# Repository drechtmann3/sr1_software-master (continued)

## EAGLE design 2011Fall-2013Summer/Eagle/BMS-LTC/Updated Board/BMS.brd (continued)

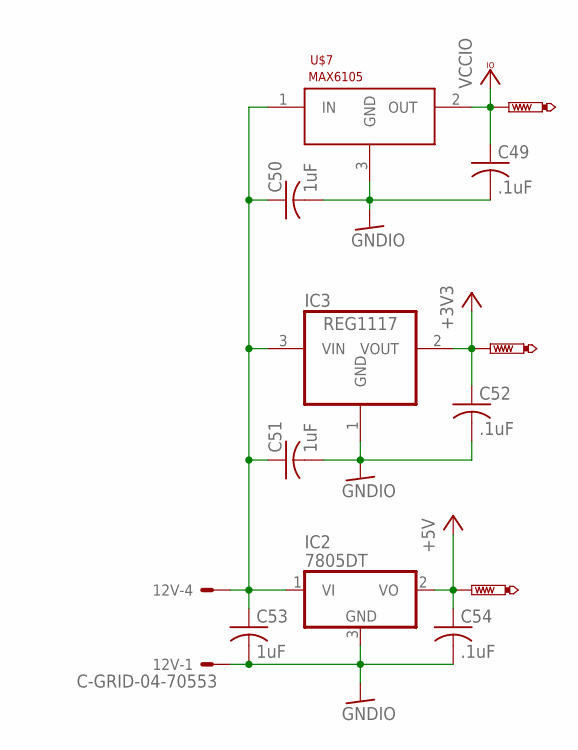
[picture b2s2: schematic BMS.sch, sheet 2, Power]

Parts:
12V: C-GRID-04-70553; 70553-04
C49, C52, C54: .1uF; C1206
C50, C51, C53: 1uF; C1206
IC2: 7805DT; TO252
IC3: REG1117; SOT223
U$7: MAX6105; SOT23
U$11, U$12, U$13: TESTPAD-20MIL; 20MIL

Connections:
12V: 12V.4, C50.1, C51.1, C53.1, IC2.1 (VI), IC3.3 (VIN), U$7.1 (IN); also elsewhere on the board
+3V3: C52.1, IC3.2 (VOUT), U$12.P$1; also elsewhere on the board
+5V: C54.1, IC2.2 (VO), U$13.P$1; also elsewhere on the board
GNDIO: 12V.1, C49.2, C50.2, C51.2, C52.2, C53.2, C54.2, IC2.3 (GND), IC3.1 (GND), U$7.3 (GND); also elsewhere on the board
VCCIO: C49.1, U$7.2 (OUT), U$11.P$1; also elsewhere on the board

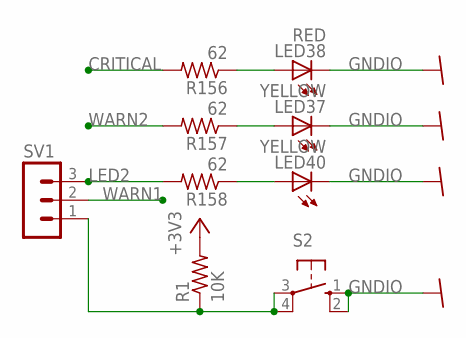
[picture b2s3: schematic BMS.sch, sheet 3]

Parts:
LED37, LED40: YELLOW; CHIPLED_1206
LED38: RED; CHIPLED_1206
R1: 10K; R1206
R156, R157, R158: 62; R1206
S2: 10-XX; B3F-10XX
SV1: MA03-1

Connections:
+3V3: R1.2; also elsewhere on the board
CRITICAL: R156.2; also elsewhere on the board
GNDIO: LED37.C, LED38.C, LED40.C, S2.1 (S), S2.2 (S1); also elsewhere on the board
LED2: R158.2, SV1.3
unnamed: R1.1, S2.3, S2.4 (P1), SV1.1
unnamed: LED37.A, R157.1
unnamed: LED38.A, R156.1
unnamed: LED40.A, R158.1
WARN1: SV1.2; also elsewhere on the board
WARN2: R157.2; also elsewhere on the board

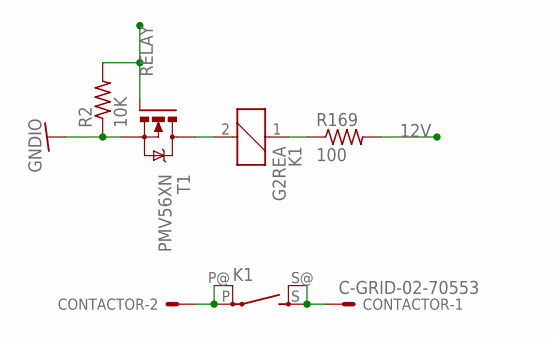
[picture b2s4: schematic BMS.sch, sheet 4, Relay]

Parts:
CONTACTOR: C-GRID-02-70553; 70553-02
K1: G2REA
R2: 10K; R1206
R169: 100; R1206
T1: PMV56XN; SOT23

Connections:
12V: R169.2; also elsewhere on the board
GNDIO: R2.1, T1.2 (S); also elsewhere on the board
unnamed: K1.2, T1.3 (D)
unnamed: K1.1, R169.1
unnamed: CONTACTOR.2, K1.P, K1.P@
unnamed: CONTACTOR.1, K1.S, K1.S@ (S)
RELAY: R2.2, T1.1 (G); also elsewhere on the board

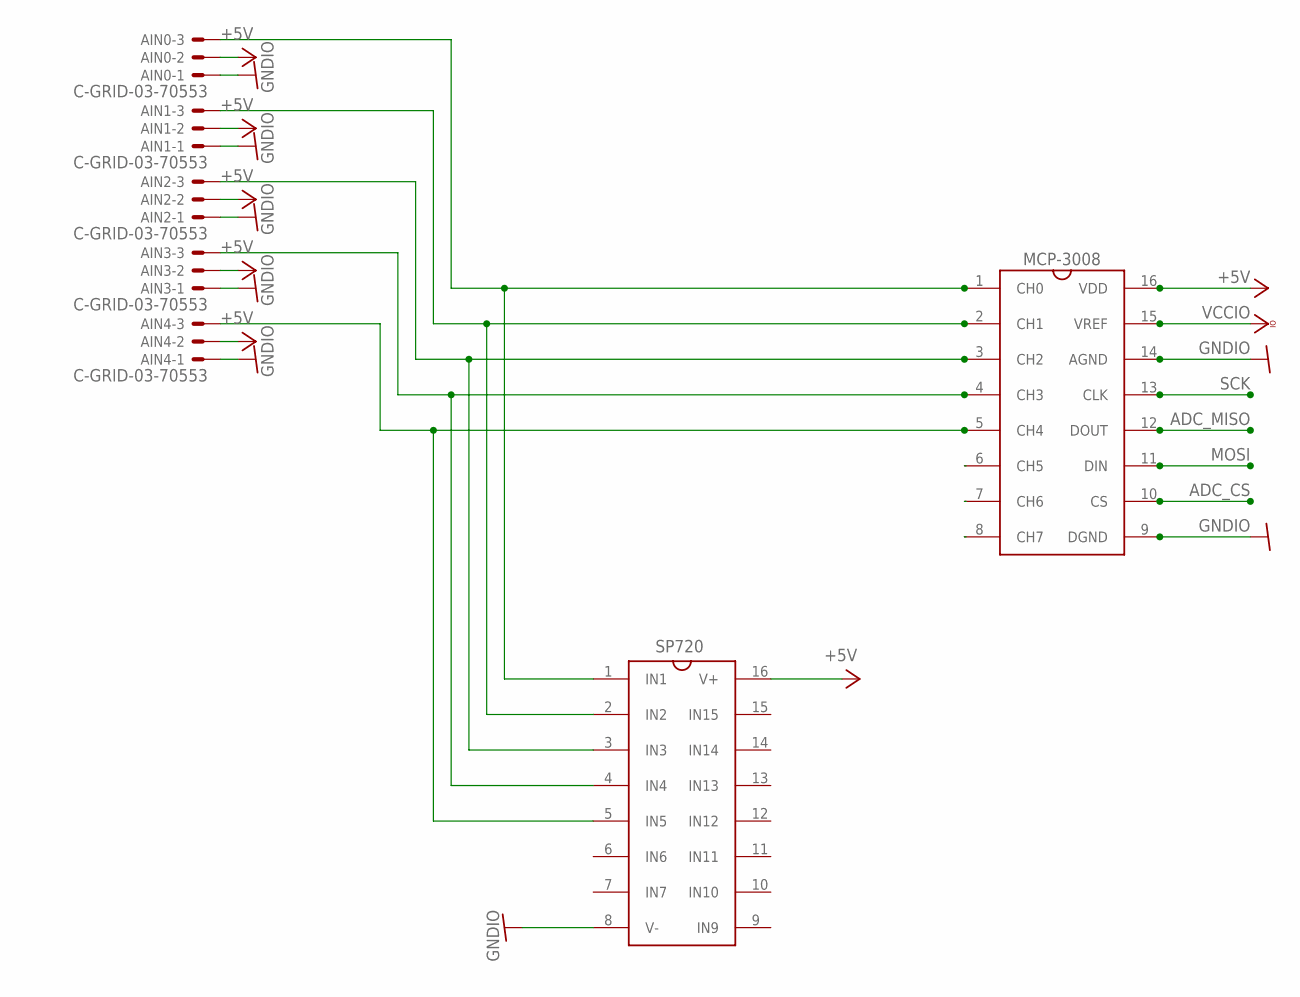
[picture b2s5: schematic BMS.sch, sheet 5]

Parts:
AIN0, AIN1, AIN2, AIN3, AIN4: C-GRID-03-70553; 70553-03
U$1: SP720APP; SO16
U$6: MCP-3008; SO16

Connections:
+5V: AIN0.2, AIN1.2, AIN2.2, AIN3.2, AIN4.2, U$1.16 (V+), U$6.16 (VDD); also elsewhere on the board
ADC_CS: U$6.10 (CS); also elsewhere on the board
ADC_MISO: U$6.12 (DOUT); also elsewhere on the board
GNDIO: AIN0.1, AIN1.1, AIN2.1, AIN3.1, AIN4.1, U$1.8 (V-), U$6.9 (DGND), U$6.14 (AGND); also elsewhere on the board
MOSI: U$6.11 (DIN); also elsewhere on the board
unnamed: AIN0.3, U$1.1 (IN1), U$6.1 (CH0)
unnamed: AIN1.3, U$1.2 (IN2), U$6.2 (CH1)
unnamed: AIN2.3, U$1.3 (IN3), U$6.3 (CH2)
unnamed: AIN3.3, U$1.4 (IN4), U$6.4 (CH3)
unnamed: AIN4.3, U$1.5 (IN5), U$6.5 (CH4)
SCK: U$6.13 (CLK); also elsewhere on the board
VCCIO: U$6.15 (VREF); also elsewhere on the board

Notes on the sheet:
MCP-3008
SP720

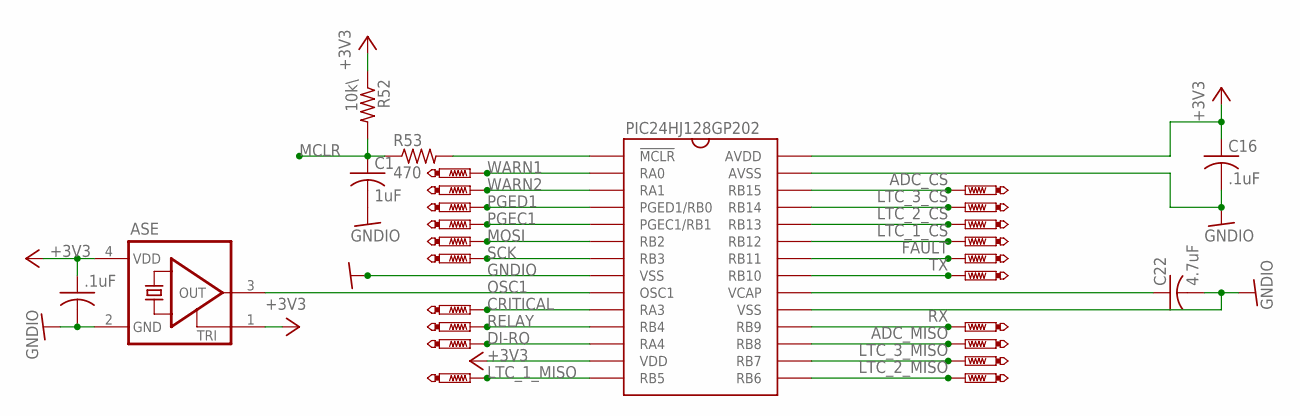
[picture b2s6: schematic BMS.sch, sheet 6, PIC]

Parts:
C1: 1uF; C1206
C16, C48: .1uF; C1206
C22: 4.7uF; C1206
R52: 10k\; R1206
R53: 470; R1206
U$2: PIC24HJ128GP-202; SO28W
U$3: ASE
U$14, U$15, U$16, U$17, U$18, U$19, U$20, U$21, U$22, U$23, U$24, U$25, U$26, U$27, U$28, U$29, U$30, U$31, U$32, U$33: TESTPAD-20MIL; 20MIL

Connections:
+3V3: C16.1, C48.1, R52.1, U$2.13 (VDD), U$2.28 (AVDD), U$3.1 (TRI), U$3.4 (VDD); also elsewhere on the board
ADC_CS: U$2.26 (RB15), U$33.P$1; also elsewhere on the board
ADC_MISO: U$2.17 (RB8), U$26.P$1; also elsewhere on the board
CRITICAL: U$2.10 (RA3), U$20.P$1; also elsewhere on the board
DI-RO: U$2.12 (RA4), U$22.P$1; also elsewhere on the board
FAULT: U$2.22 (RB11), U$29.P$1; also elsewhere on the board
GNDIO: C1.2, C16.2, C22.2, C48.2, U$2.8 (VSS), U$2.19 (VSS), U$2.27 (AVSS), U$3.2 (GND); also elsewhere on the board
LTC_1_CS: U$2.23 (RB12), U$30.P$1; also elsewhere on the board
LTC_1_MISO: U$2.14 (RB5), U$23.P$1; also elsewhere on the board
LTC_2_CS: U$2.24 (RB13), U$31.P$1; also elsewhere on the board
LTC_2_MISO: U$2.15 (RB6), U$24.P$1; also elsewhere on the board
LTC_3_CS: U$2.25 (RB14), U$32.P$1; also elsewhere on the board
LTC_3_MISO: U$2.16 (RB7), U$25.P$1; also elsewhere on the board
MCLR: C1.1, R52.2, R53.1; also elsewhere on the board
MOSI: U$2.6 (RB2), U$18.P$1; also elsewhere on the board
unnamed: R53.2, U$2.1 (!MCLR!)
unnamed: C22.1, U$2.20 (VCAP)
OSC1: U$2.9 (OSC1), U$3.3 (OUT); also elsewhere on the board
PGEC1: U$2.5 (PGEC1/RB1), U$17.P$1; also elsewhere on the board
PGED1: U$2.4 (PGED1/RB0), U$16.P$1; also elsewhere on the board
RELAY: U$2.11 (RB4), U$21.P$1; also elsewhere on the board
RX: U$2.18 (RB9), U$27.P$1; also elsewhere on the board
SCK: U$2.7 (RB3), U$19.P$1; also elsewhere on the board
TX: U$2.21 (RB10), U$28.P$1; also elsewhere on the board
WARN1: U$2.2 (RA0), U$14.P$1; also elsewhere on the board
WARN2: U$2.3 (RA1), U$15.P$1; also elsewhere on the board

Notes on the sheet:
PIC24HJ128GP202

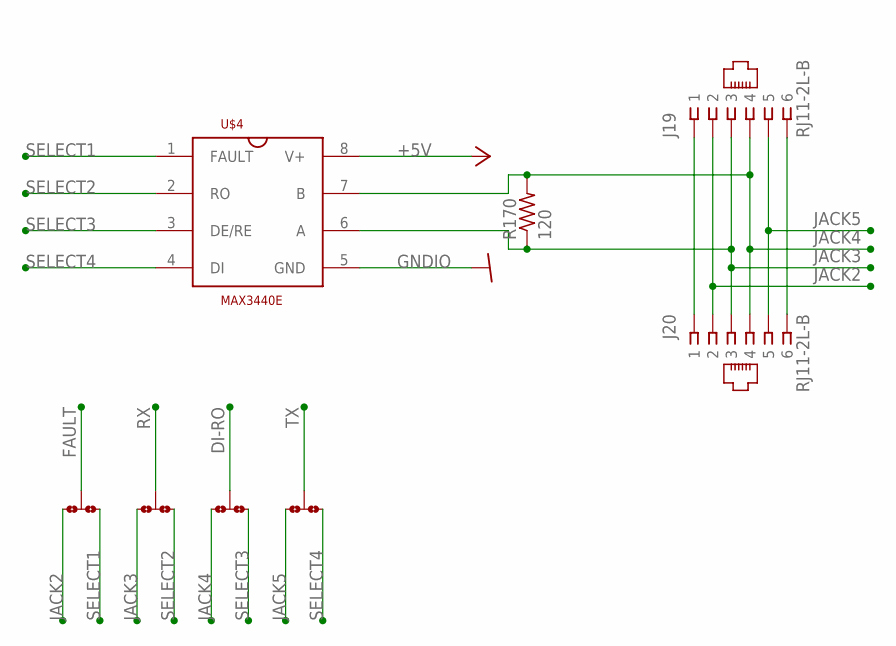
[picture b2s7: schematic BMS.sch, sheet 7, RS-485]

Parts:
J19, J20: RJ11-2L-B; RJ11-NO_SHIELD
R170: 120; R1206
U$4: MAX3440E; SO-08
U$5: 3ROW_4POS

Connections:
+5V: U$4.8 (V+); also elsewhere on the board
DI-RO: U$5.8 (2); also elsewhere on the board
FAULT: U$5.2; also elsewhere on the board
GNDIO: U$4.5 (GND); also elsewhere on the board
JACK2: J19.2, J20.2, U$5.1
JACK3: J19.3, J20.3, R170.1, U$4.6 (A), U$5.4 (1)
JACK4: J19.4, J20.4, R170.2, U$4.7 (B), U$5.7 (1)
JACK5: J19.5, J20.5, U$5.10 (1)
unnamed: J19.1, J20.1
unnamed: J19.6, J20.6
RX: U$5.5 (2); also elsewhere on the board
SELECT1: U$4.1 (FAULT), U$5.3
SELECT2: U$4.2 (RO), U$5.6 (3)
SELECT3: U$4.3 (DE/RE), U$5.9 (3)
SELECT4: U$4.4 (DI), U$5.12 (3)
TX: U$5.11 (2); also elsewhere on the board

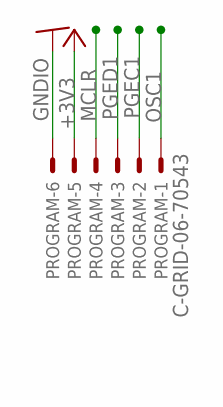
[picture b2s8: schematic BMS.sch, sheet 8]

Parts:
PROGRAM: C-GRID-06-70543; 70543-06

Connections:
+3V3: PROGRAM.5; also elsewhere on the board
GNDIO: PROGRAM.6; also elsewhere on the board
MCLR: PROGRAM.4; also elsewhere on the board
OSC1: PROGRAM.1; also elsewhere on the board
PGEC1: PROGRAM.2; also elsewhere on the board
PGED1: PROGRAM.3; also elsewhere on the board

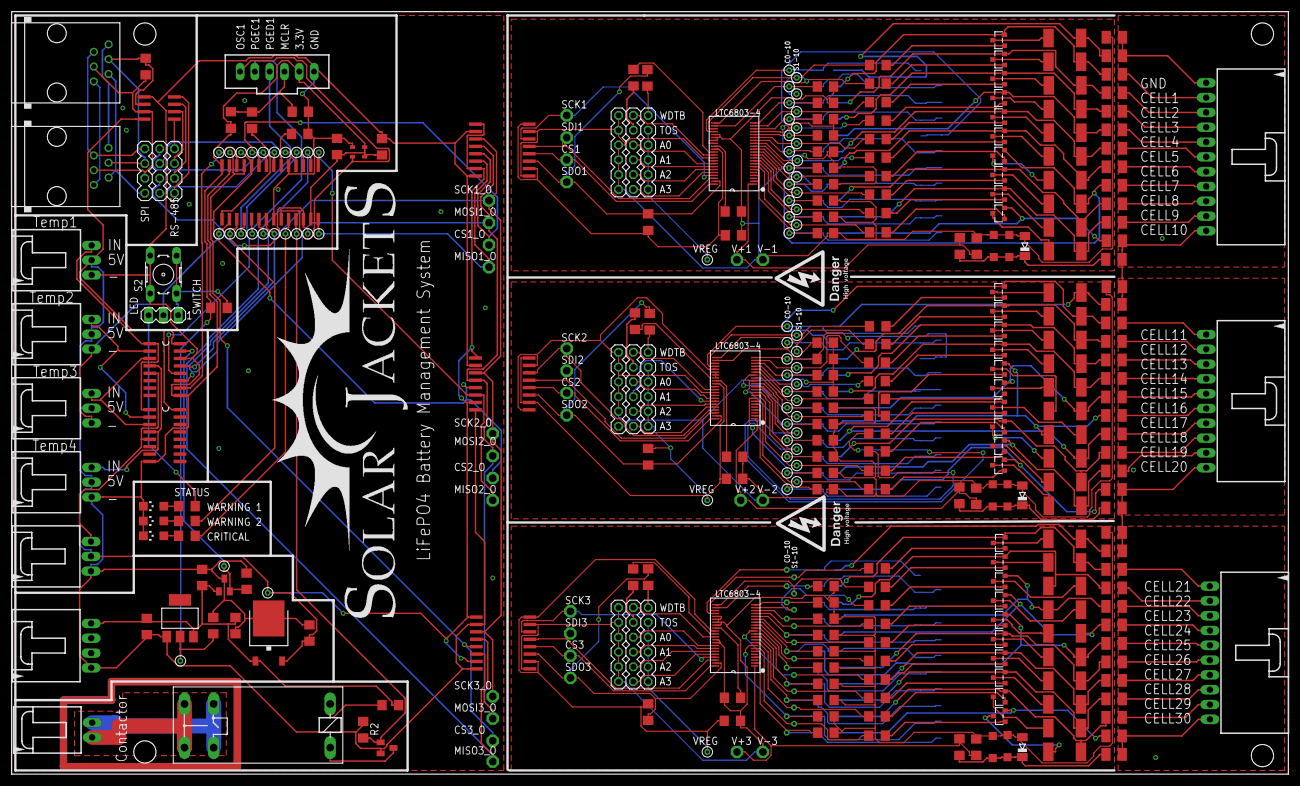
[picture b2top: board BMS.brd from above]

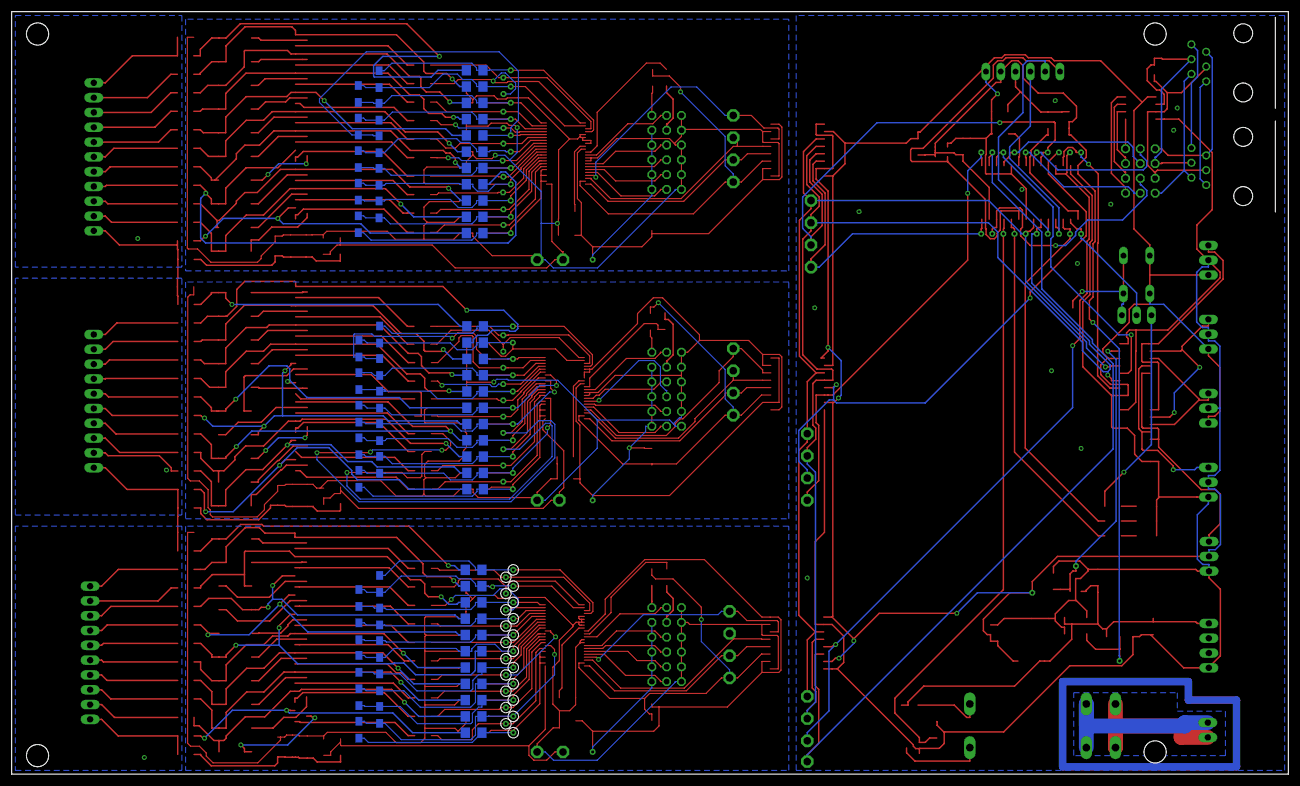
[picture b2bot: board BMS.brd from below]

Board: 2 copper layers, 219.1 x 130.8 mm, 428 parts (84 on the bottom side), 291 nets.

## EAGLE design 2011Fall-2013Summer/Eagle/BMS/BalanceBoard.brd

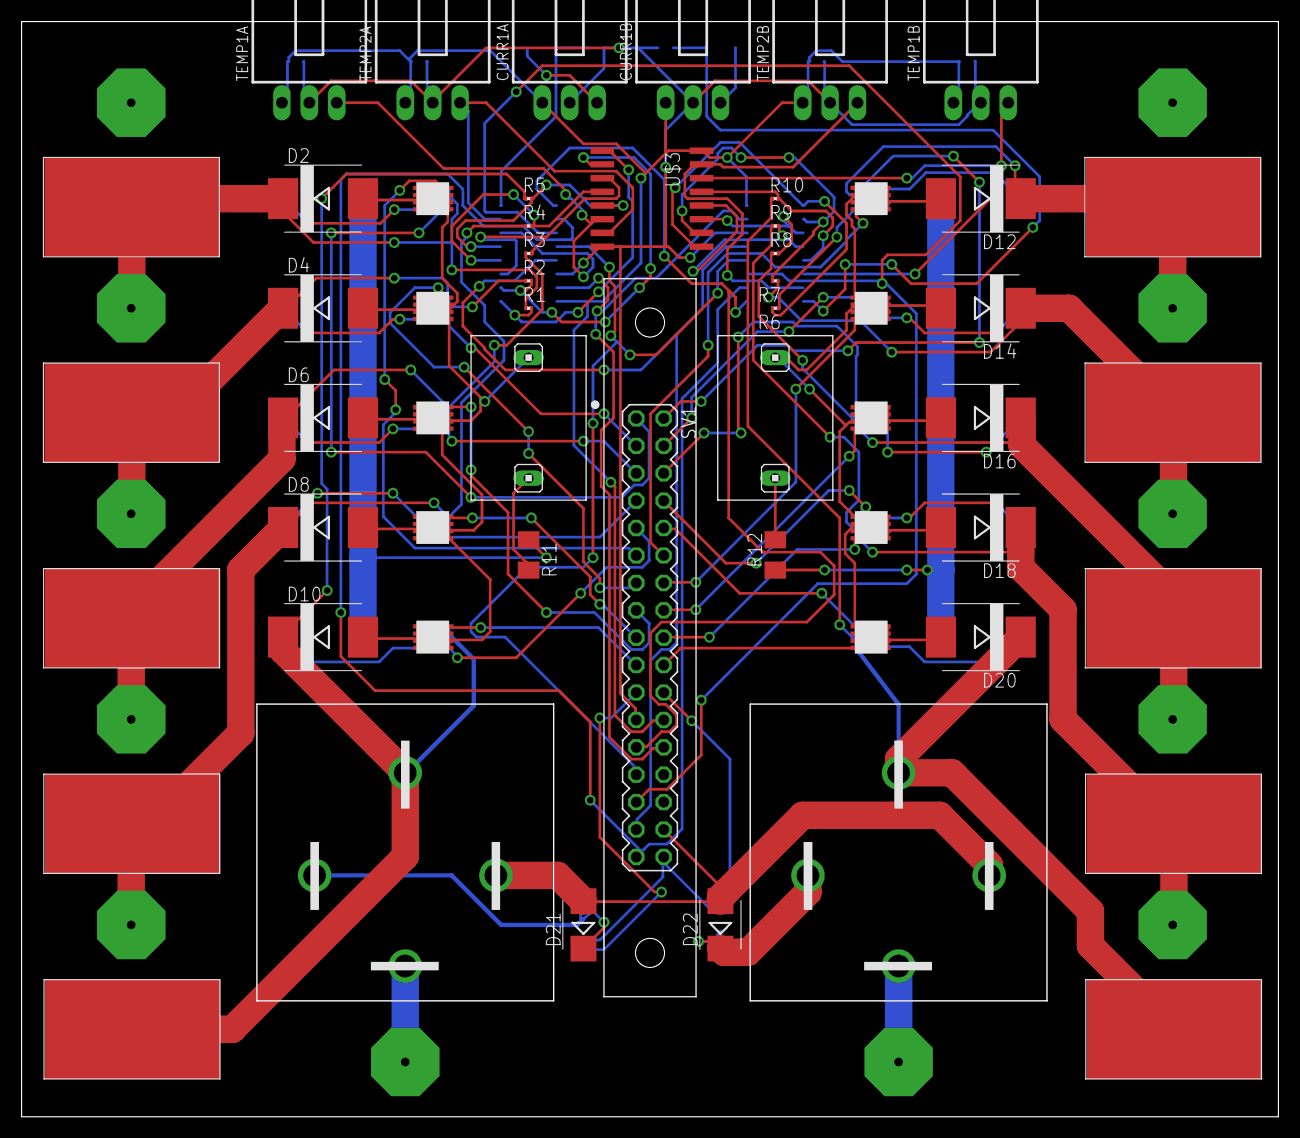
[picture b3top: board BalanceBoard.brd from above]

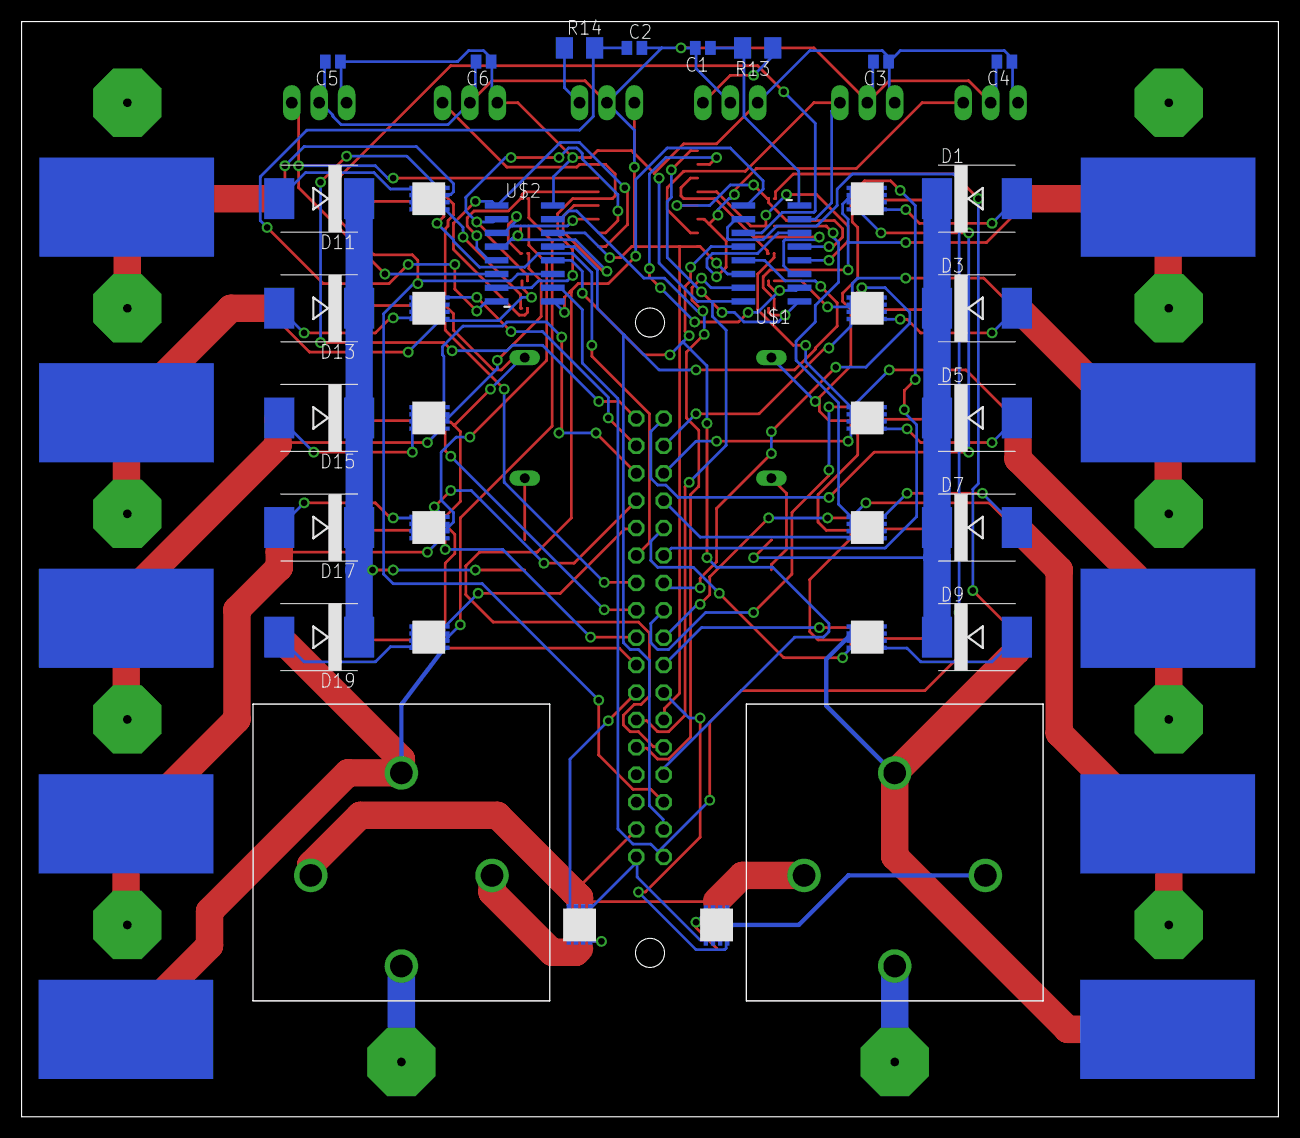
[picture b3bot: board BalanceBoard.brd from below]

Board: 2 copper layers, 116.5 x 101.5 mm, 100 parts (32 on the bottom side), 90 nets.

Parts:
C1, C2, C3, C4, C5, C6: 0.1uF; C0504
CURR1A, CURR1B: C-GRID-03-70553; 70553-03
D1, D2, D3, D4, D5, D6, D7, D8, D9, D10, D11, D12, D13, D14, D15, D16, D17, D18, D19, D20: SMC
D21, D22: SMB
L1, L2: INDUCTOR_SOCKET
R1, R2, R3, R4, R5, R6, R7, R8, R9, R10: 3.3M; R0201
R11, R12: M1206
R13, R14: 1K; M1206
SV1: MA17-2
TEMP1A, TEMP1B, TEMP2A, TEMP2B: C-GRID-03-70553; 70553-03
U$1, U$2: MCP3008; SOIC16N
U$3: SP720APP; SO16W
U$4, U$5, U$6, U$7, U$8, U$9, U$10, U$11, U$12, U$13, U$23, U$26, U$27, U$30, U$31, U$32, U$33, U$34, U$35, U$36, U$37, U$38: SIS322DNT-T1-GE3POWERPAK1212-8; POWERPAK1212-8
U$14, U$15, U$16, U$17, U$18, U$40, U$41, U$42, U$43, U$44: MOLEXCONN-SCREWHOLE
U$20, U$22, U$24, U$25, U$28, U$29, U$46, U$47, U$48, U$49, U$50, U$51: MOLEXCONN-SCREWHOLE-NEG
U$21, U$39: PB1039

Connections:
12V+: SV1.34, U$23.SOURCE1, U$23.SOURCE2, U$23.SOURCE3, U$38.SOURCE1, U$38.SOURCE2, U$38.SOURCE3
12V-: D21.A, D22.A, SV1.32, U$21.P$2, U$39.P$2
AGND_PLANE: C1.2, C2.2, C3.2, C4.2, C5.2, C6.2, CURR1A.2, CURR1B.2, SV1.23, TEMP1A.2, TEMP1B.2, TEMP2A.2, TEMP2B.2, U$1.14, U$2.14, U$3.8
CH0A: D2.C, R1.1, U$4.SOURCE1, U$4.SOURCE2, U$4.SOURCE3, U$14.P$1, U$22.P$1
CH0B: D12.C, R6.1, U$26.SOURCE1, U$26.SOURCE2, U$26.SOURCE3, U$40.P$1, U$47.P$1
CH1A: D4.C, R2.1, U$6.SOURCE1, U$6.SOURCE2, U$6.SOURCE3, U$15.P$1, U$24.P$1
CH1B: D14.C, R7.1, U$30.SOURCE1, U$30.SOURCE2, U$30.SOURCE3, U$41.P$1, U$48.P$1
CH2A: D6.C, R3.1, U$8.SOURCE1, U$8.SOURCE2, U$8.SOURCE3, U$16.P$1, U$25.P$1
CH2B: D16.C, R8.1, U$32.SOURCE1, U$32.SOURCE2, U$32.SOURCE3, U$42.P$1, U$49.P$1
CH3A: D8.C, R4.1, U$10.SOURCE1, U$10.SOURCE2, U$10.SOURCE3, U$17.P$1, U$28.P$1
CH3B: D18.C, R9.1, U$34.SOURCE1, U$34.SOURCE2, U$34.SOURCE3, U$43.P$1, U$50.P$1
CH4A: D10.C, R5.1, U$12.SOURCE1, U$12.SOURCE2, U$12.SOURCE3, U$18.P$1, U$21.P$4
CH4B: D20.C, R10.1, U$36.SOURCE1, U$36.SOURCE2, U$36.SOURCE3, U$39.P$4, U$44.P$1
CH5A: TEMP1A.3, U$1.6, U$3.6
CH5B: TEMP1B.3, U$2.6, U$3.14
CH6A: TEMP2A.3, U$1.7, U$3.7
CH6B: TEMP2B.3, U$2.7, U$3.15
CH7A: C1.1, R13.2, U$1.8
CH7B: C2.1, R14.2, U$2.8
CLK: SV1.31, U$1.13, U$2.13
CS: SV1.33, U$1.10, U$2.10
DGND: SV1.25, U$1.9, U$2.9
DIN: SV1.29, U$1.11, U$2.11
DOUT: SV1.27, U$1.12, U$2.12
unnamed: R5.2, U$1.5, U$3.5
unnamed: R4.2, U$1.4, U$3.4
unnamed: R3.2, U$1.3, U$3.3
unnamed: R2.2, U$1.2, U$3.2
unnamed: R1.2, U$1.1, U$3.1
unnamed: CURR1A.3, R13.1
unnamed: CURR1B.3, R14.1
unnamed: D1.A, U$4.DRAIN5, U$4.DRAIN6, U$4.DRAIN7, U$4.DRAIN8, U$4.DRAIN_ALL
unnamed: R10.2, U$2.5, U$3.13
unnamed: R9.2, U$2.4, U$3.12
unnamed: R8.2, U$2.3, U$3.11
unnamed: R7.2, U$2.2, U$3.10
unnamed: R6.2, U$2.1, U$3.9
unnamed: D2.A, U$5.DRAIN5, U$5.DRAIN6, U$5.DRAIN7, U$5.DRAIN8, U$5.DRAIN_ALL
unnamed: D21.C, U$21.P$3, U$23.DRAIN5, U$23.DRAIN6, U$23.DRAIN7, U$23.DRAIN8, U$23.DRAIN_ALL
unnamed: L1.P$1, R11.2
unnamed: D3.A, U$6.DRAIN5, U$6.DRAIN6, U$6.DRAIN7, U$6.DRAIN8, U$6.DRAIN_ALL
unnamed: D4.A, U$7.DRAIN5, U$7.DRAIN6, U$7.DRAIN7, U$7.DRAIN8, U$7.DRAIN_ALL
unnamed: U$21.P$1, U$29.P$1
unnamed: D11.A, U$26.DRAIN5, U$26.DRAIN6, U$26.DRAIN7, U$26.DRAIN8, U$26.DRAIN_ALL
unnamed: D5.A, U$8.DRAIN5, U$8.DRAIN6, U$8.DRAIN7, U$8.DRAIN8, U$8.DRAIN_ALL
unnamed: D6.A, U$9.DRAIN5, U$9.DRAIN6, U$9.DRAIN7, U$9.DRAIN8, U$9.DRAIN_ALL
unnamed: D12.A, U$27.DRAIN5, U$27.DRAIN6, U$27.DRAIN7, U$27.DRAIN8, U$27.DRAIN_ALL
unnamed: D7.A, U$10.DRAIN5, U$10.DRAIN6, U$10.DRAIN7, U$10.DRAIN8, U$10.DRAIN_ALL
unnamed: D8.A, U$11.DRAIN5, U$11.DRAIN6, U$11.DRAIN7, U$11.DRAIN8, U$11.DRAIN_ALL
unnamed: D13.A, U$30.DRAIN5, U$30.DRAIN6, U$30.DRAIN7, U$30.DRAIN8, U$30.DRAIN_ALL
unnamed: D9.A, U$12.DRAIN5, U$12.DRAIN6, U$12.DRAIN7, U$12.DRAIN8, U$12.DRAIN_ALL
unnamed: D10.A, U$13.DRAIN5, U$13.DRAIN6, U$13.DRAIN7, U$13.DRAIN8, U$13.DRAIN_ALL
unnamed: D14.A, U$31.DRAIN5, U$31.DRAIN6, U$31.DRAIN7, U$31.DRAIN8, U$31.DRAIN_ALL
unnamed: D15.A, U$32.DRAIN5, U$32.DRAIN6, U$32.DRAIN7, U$32.DRAIN8, U$32.DRAIN_ALL
unnamed: D16.A, U$33.DRAIN5, U$33.DRAIN6, U$33.DRAIN7, U$33.DRAIN8, U$33.DRAIN_ALL
unnamed: D17.A, U$34.DRAIN5, U$34.DRAIN6, U$34.DRAIN7, U$34.DRAIN8, U$34.DRAIN_ALL
unnamed: D18.A, U$35.DRAIN5, U$35.DRAIN6, U$35.DRAIN7, U$35.DRAIN8, U$35.DRAIN_ALL
unnamed: D19.A, U$36.DRAIN5, U$36.DRAIN6, U$36.DRAIN7, U$36.DRAIN8, U$36.DRAIN_ALL
unnamed: D20.A, U$37.DRAIN5, U$37.DRAIN6, U$37.DRAIN7, U$37.DRAIN8, U$37.DRAIN_ALL
unnamed: L2.P$2, U$27.SOURCE1, U$27.SOURCE2, U$27.SOURCE3, U$31.SOURCE1, U$31.SOURCE2, U$31.SOURCE3, U$33.SOURCE1, U$33.SOURCE2, U$33.SOURCE3, U$35.SOURCE1, U$35.SOURCE2, U$35.SOURCE3, U$37.SOURCE1, U$37.SOURCE2, U$37.SOURCE3
unnamed: U$39.P$1, U$51.P$1
unnamed: D22.C, U$38.DRAIN5, U$38.DRAIN6, U$38.DRAIN7, U$38.DRAIN8, U$38.DRAIN_ALL, U$39.P$3
unnamed: D11.C, D13.C, D15.C, D17.C, D19.C, R12.1
unnamed: L2.P$1, R12.2
unnamed: L1.P$2, U$5.SOURCE1, U$5.SOURCE2, U$5.SOURCE3, U$7.SOURCE1, U$7.SOURCE2, U$7.SOURCE3, U$9.SOURCE1, U$9.SOURCE2, U$9.SOURCE3, U$11.SOURCE1, U$11.SOURCE2, U$11.SOURCE3, U$13.SOURCE1, U$13.SOURCE2, U$13.SOURCE3
unnamed: D1.C, D3.C, D5.C, D7.C, D9.C, R11.1
RELAYA: SV1.21, U$23.GATE
RELAYB: SV1.22, U$38.GATE
VDD_PLANE: C3.1, C4.1, C5.1, C6.1, CURR1A.1, CURR1B.1, SV1.24, TEMP1A.1, TEMP1B.1, TEMP2A.1, TEMP2B.1, U$1.16, U$2.16, U$3.16
VREF: SV1.26, U$1.15, U$2.15
X0A: SV1.1, U$4.GATE
X0B: SV1.2, U$26.GATE
X1A: SV1.3, U$6.GATE
X1B: SV1.4, U$30.GATE
X2A: SV1.5, U$8.GATE
X2B: SV1.6, U$32.GATE
X3A: SV1.7, U$10.GATE
X3B: SV1.8, U$34.GATE
X4A: SV1.9, U$12.GATE
X4B: SV1.10, U$36.GATE
Y0A: SV1.11, U$5.GATE
Y0B: SV1.12, U$27.GATE
Y1A: SV1.13, U$7.GATE
Y1B: SV1.14, U$31.GATE
Y2A: SV1.15, U$9.GATE
Y2B: SV1.16, U$33.GATE
Y3A: SV1.17, U$11.GATE
Y3B: SV1.18, U$35.GATE
Y4A: SV1.19, U$13.GATE
Y4B: SV1.20, U$37.GATE

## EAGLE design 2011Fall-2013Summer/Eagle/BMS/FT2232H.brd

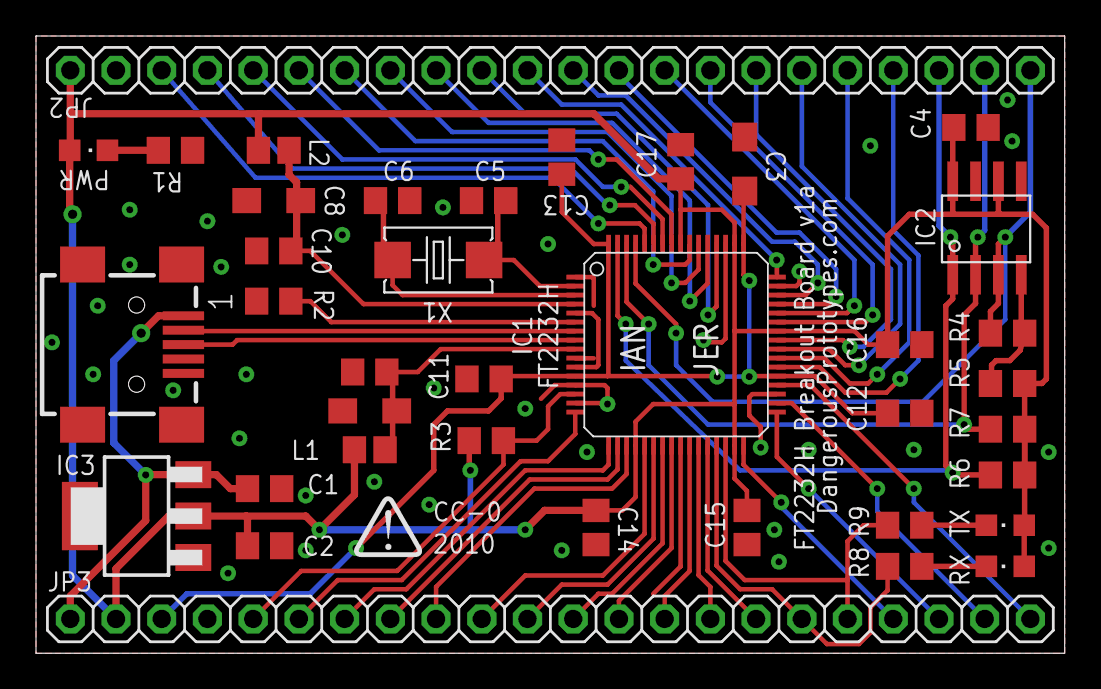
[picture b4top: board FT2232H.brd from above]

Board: 2 copper layers, 57.1 x 34.3 mm, 39 parts (0 on the bottom side), 53 nets.

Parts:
C1, C2, C4, C9, C10, C11, C12, C13, C14, C15, C16, C17: 0.1uF; C805
C3: 3.3uF; SMC_A
C5, C6: 27pF; C805
C7, C8: 4.7uF; SMC_A
CONN1: CONN_USB; CONN_USB_MINI-B
IC1: FT2232H; LQFP64
IC2: 93C46; SOIC8
IC3: SOT223
JP2, JP3: 1X22
L1, L2: FB805
PWR: LED-805
R1, R8, R9: 470; R805
R2: 12k 1%; R805
R3, R5, R6, R7: 10k; R805
R4: 2.2k; R805
RX: LED-805
TX: LED-805
U$7: DP_LOGO
X1: 12MHz; 4X6

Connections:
1.8V: C3.+, C11.1, C12.1, C13.1, IC1.12, IC1.37, IC1.49, IC1.64, JP3.3
3.3V: C2.1, C4.1, C14.1, C15.1, C16.1, C17.1, IC1.20, IC1.31, IC1.42, IC1.50, IC1.56, IC2.6, IC2.8, IC3.2, JP2.1, JP3.2, L1.2, L2.2, PWR.A, R3.1, R5.2, R6.2, R7.2, RX.A, TX.A
5V: C1.1, CONN1.VUSB, IC3.3, JP3.1
!PWEREN: IC1.60, JP2.3
!RESET: IC1.14, JP3.5, R3.2
!SUSPEND: IC1.36, JP3.22
AC0: IC1.26, JP3.14
AC1: IC1.27, JP3.15
AC2: IC1.28, JP3.16
AC3: IC1.29, JP3.17, R8.1
AC4: IC1.30, JP3.18, R9.1
AC5: IC1.32, JP3.19
AC6: IC1.33, JP3.20
AC7: IC1.34, JP3.21
AD0: IC1.16, JP3.6
AD1: IC1.17, JP3.7
AD2: IC1.18, JP3.8
AD3: IC1.19, JP3.9
AD4: IC1.21, JP3.10
AD5: IC1.22, JP3.11
AD6: IC1.23, JP3.12
AD7: IC1.24, JP3.13
BC0: IC1.48, JP2.11
BC1: IC1.52, JP2.10
BC2: IC1.53, JP2.9
BC3: IC1.54, JP2.8
BC4: IC1.55, JP2.7
BC5: IC1.57, JP2.6
BC6: IC1.58, JP2.5
BC7: IC1.59, JP2.4
BD0: IC1.38, JP2.19
BD1: IC1.39, JP2.18
BD2: IC1.40, JP2.17
BD3: IC1.41, JP2.16
BD4: IC1.43, JP2.15
BD5: IC1.44, JP2.14
BD6: IC1.45, JP2.13
BD7: IC1.46, JP2.12
DM: CONN1.D-, IC1.7
DP: CONN1.D+, IC1.8
EECLK: IC1.62, IC2.2, JP2.21, R7.1
EECS: IC1.63, IC2.1, JP2.20, R6.1
EEDATA: IC1.61, IC2.3, JP2.22, R4.2
GND: C1.2, C2.2, C3.-, C4.2, C5.2, C6.2, C7.-, C8.-, C9.2, C10.2, C11.2, C12.2, C13.2, C14.2, C15.2, C16.2, C17.2, CONN1.GND, IC1.1, IC1.5, IC1.10, IC1.11, IC1.13, IC1.15, IC1.25, IC1.35, IC1.47, IC1.51, IC2.5, IC3.1, JP2.2, JP3.4, R1.1, R2.1
unnamed: PWR.C, R1.2
unnamed: R8.2, RX.C
unnamed: R9.2, TX.C
unnamed: IC1.6, R2.2
unnamed: C5.1, IC1.2, X1.1
unnamed: C6.1, IC1.3, X1.2
unnamed: IC2.4, R4.1, R5.1
unnamed: C8.+, C10.1, IC1.4, L2.1
unnamed: C7.+, C9.1, IC1.9, L1.1

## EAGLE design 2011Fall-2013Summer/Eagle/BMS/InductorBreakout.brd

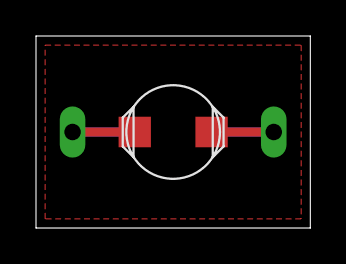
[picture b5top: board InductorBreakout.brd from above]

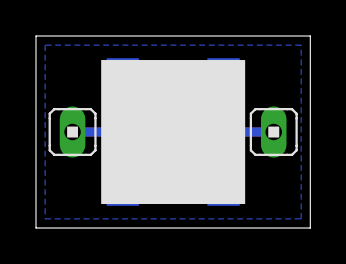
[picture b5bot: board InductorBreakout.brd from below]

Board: 2 copper layers, 15.2 x 10.7 mm, 4 parts (3 on the bottom side), 2 nets.

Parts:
NEWBATT: LQH55PN220MR0L
OLDBATT: NRS8040T0R9NJGJ
U$5, U$6: SINGLE_HEADER

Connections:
unnamed: NEWBATT.P$2, OLDBATT.P$2, U$5.P$1
unnamed: NEWBATT.P$1, OLDBATT.P$1, U$6.P$1

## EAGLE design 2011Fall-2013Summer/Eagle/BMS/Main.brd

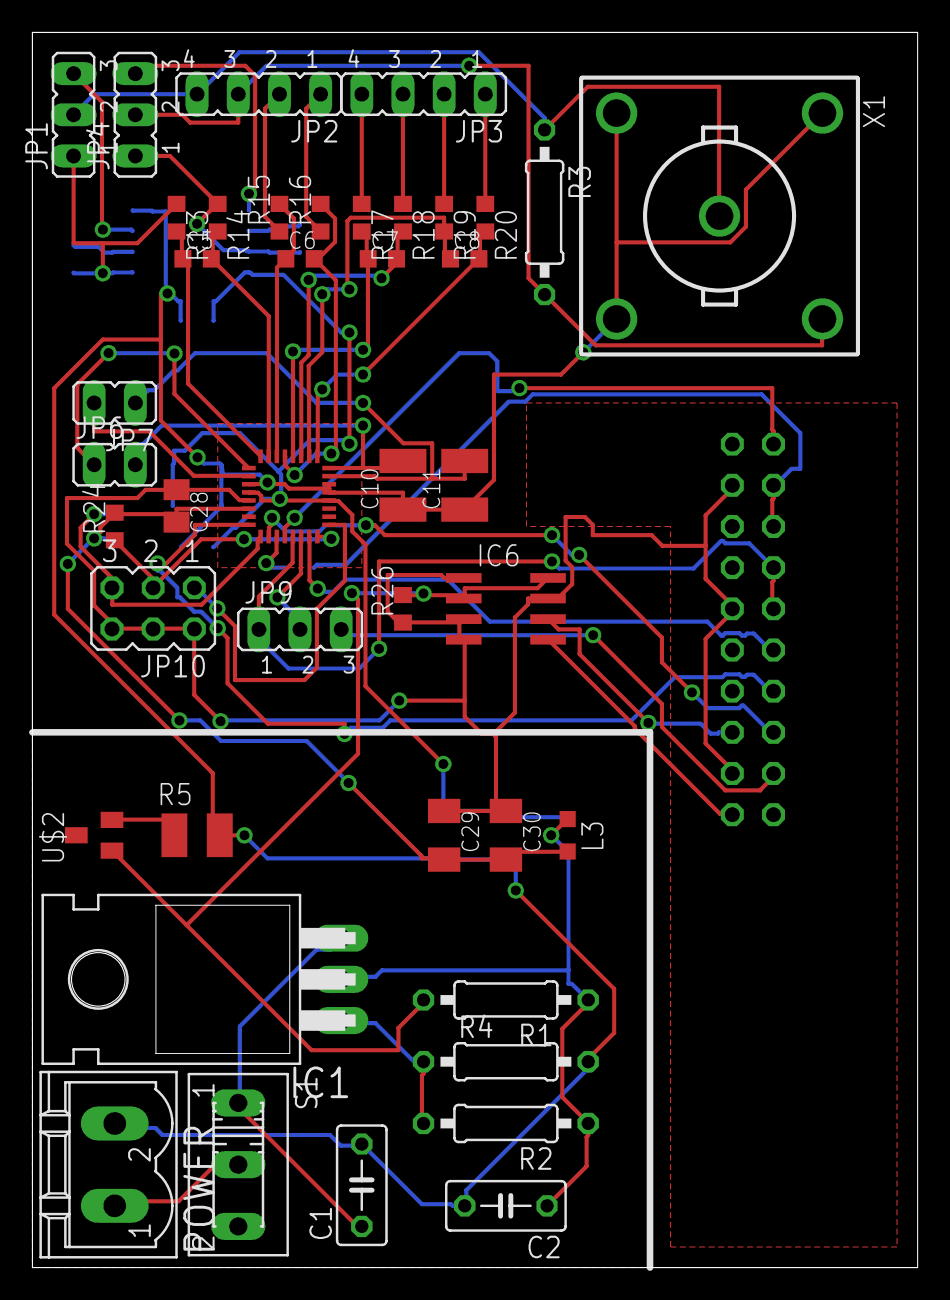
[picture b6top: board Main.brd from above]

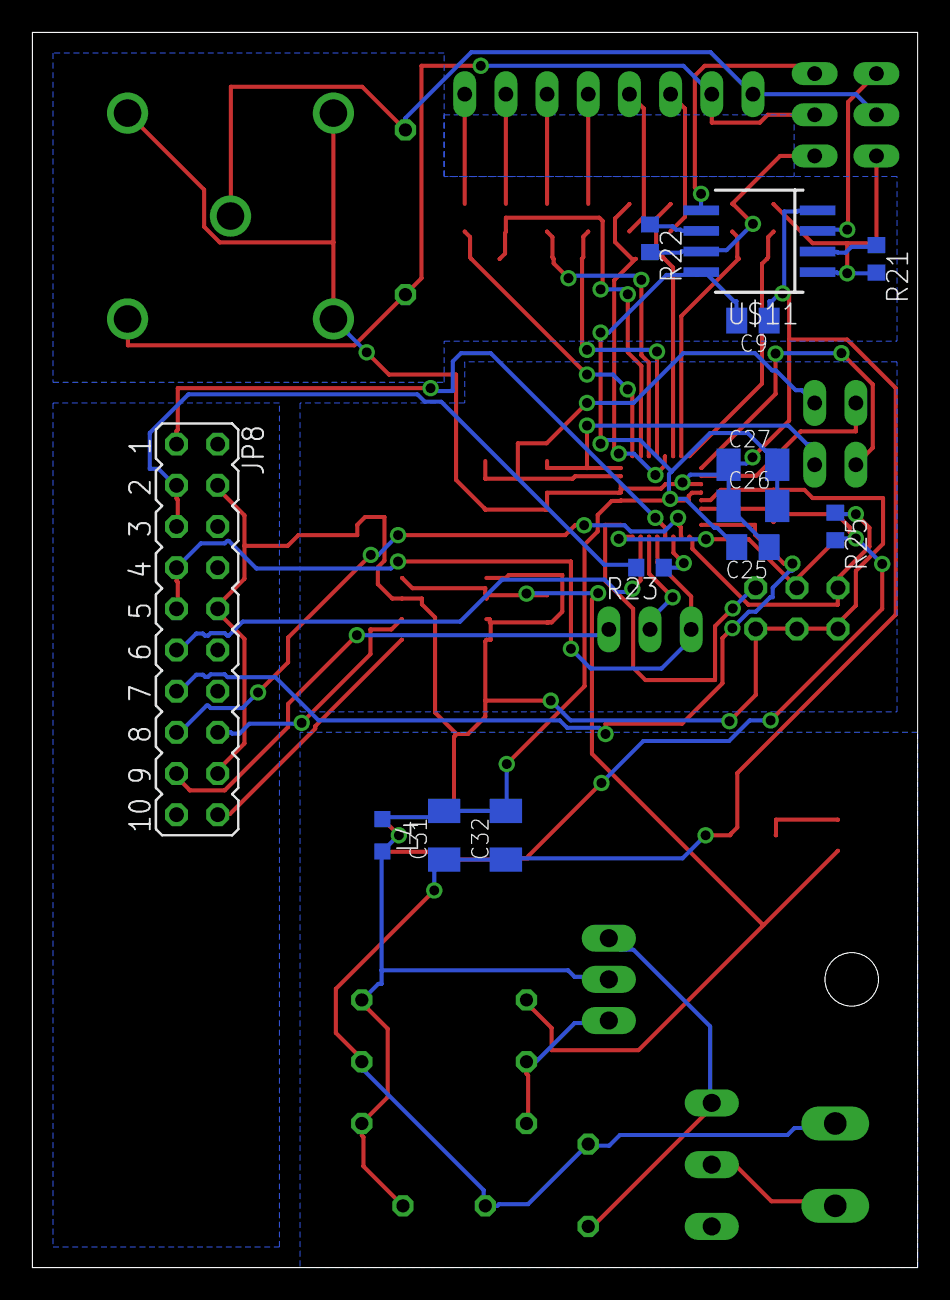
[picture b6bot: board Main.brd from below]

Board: 2 copper layers, 54.6 x 76.2 mm, 55 parts (13 on the bottom side), 50 nets.

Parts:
C1, C2: C050-030X075
C5, C6, C7, C8: 3900pF; C0603K
C9, C25, C28: 1uF; C0805K
C10, C11: 10uF; C1210K
C26, C27, C29, C30, C31, C32: 0.1uF; C1206K
IC1: 317T; TO220H
IC6: 24LC256T; SO-08
JP1, JP4, JP9: JP2
JP2, JP3: JP4
JP6, JP7: JP1
JP8: JP10Q
JP10: JP3Q
L3, L4: L2012C
POWER: MSTBV2
R1: 150; 0207/10
R2: 240; 0207/10
R3: 1M; 0207/10
R4: 725; 0207/10
R5: 0; R3225
R13, R14, R15, R16, R17, R18, R19, R20, R21, R22: 49.9; R0603
R23, R26: 33; R0603
R24, R25: 10K; R0603
S1: 255SB
U$1: ADS8386; ADS8363
U$2: LM4040; SOT23
U$11: OPA2365; SOP-08
X1: B35N57

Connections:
3.3V+: IC6.2, IC6.8, R1.2, R26.2, U$2.1
5V+: C9.2, C25.2, C26.2, C27.2, C31.2, C32.2, L4.1, U$1.P$13_, U$1.P$29_, U$11.8
D5V+: C28.2, C29.2, C30.2, L3.2, R24.2, R25.2, U$1.P$27_
DC+: POWER.1, S1.2
DGND0: C28.1, C29.1, C30.1, IC6.1, IC6.3, IC6.4, IC6.7, JP8.4, JP8.10, JP8.18, JP10.2, JP10.4, JP10.6, R26.1, U$1.P$28_
GND: R5.1, U$2.2
GND0: C1.2, C2.2, C9.1, C10.1, C11.1, C25.1, C26.1, C27.1, C31.1, C32.1, POWER.2, R4.2, R5.2, U$1.P$11_, U$1.P$12_, U$1.P$30_, U$11.4, X1.3, X1.4, X1.5
unnamed: C5.1, R13.2, U$1.P$1_
unnamed: C5.2, R14.2, U$1.P$2_
unnamed: C6.1, R15.2, U$1.P$3_
unnamed: C6.2, R16.2, U$1.P$4_
unnamed: C7.1, R17.2, U$1.P$5_
unnamed: C7.2, R18.2, U$1.P$6_
unnamed: C8.1, R19.2, U$1.P$7_
unnamed: C8.2, R20.2, U$1.P$8_
unnamed: JP1.1, R13.1, R21.2, U$11.1
unnamed: R21.1, U$11.2
unnamed: JP1.3, U$11.3
unnamed: C2.1, IC1.2, L3.1, L4.2, R1.1, R2.1
unnamed: JP4.1, R14.1, R22.2, U$11.7
unnamed: R22.1, U$11.6
unnamed: JP4.3, U$11.5
unnamed: JP2.2, R15.1
unnamed: JP2.1, R16.1
unnamed: JP3.4, R17.1
unnamed: JP3.3, R18.1
unnamed: JP3.2, R19.1
unnamed: JP3.1, R20.1
unnamed: C10.2, JP6.2, U$1.P$9_
unnamed: JP6.1, U$1.P$32_
unnamed: JP7.2, U$1.P$31_
unnamed: C11.2, JP7.1, U$1.P$10_
unnamed: JP8.1, U$1.P$21_
unnamed: R23.1, U$1.P$22_
unnamed: JP8.3, JP8.5, R23.2
unnamed: JP8.7, JP8.9, JP9.1, U$1.P$20_
unnamed: JP8.11, U$1.P$18_
unnamed: JP8.13, U$1.P$25_
unnamed: JP8.15, U$1.P$23_
unnamed: JP9.2, U$1.P$19_
unnamed: JP8.17, JP9.3
unnamed: JP10.1, U$1.P$16_
unnamed: JP10.3, R24.1, U$1.P$17_
unnamed: JP10.5, R25.1, U$1.P$24_
unnamed: IC6.5, JP8.20
unnamed: IC6.6, JP8.16
unnamed: C1.1, IC1.3, S1.1
unnamed: IC1.1, R2.2, R4.1
SIGNALGND: JP2.3, JP4.2, R3.2, X1.2
SIGNALV+: JP1.2, JP2.4, R3.1, X1.1
